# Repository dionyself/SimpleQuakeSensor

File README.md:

# Simple Quake Sensor 
SimpleQuake Sensor is an Earthquake Analyzer. (Work in Progress)  
Useful to capture and analyze Natural EM wave emitions and Earthquake EM emitions.  
The circuit works as an EM ear and broadband receiver  

### Primary EM waves 0 - 40 Hz  
- Ultra Low Frequency: f < 3 Hz  
- Extremely Low Frequency: 3 Hz < f < 3 kHz  
- Very Low Frequency: 3 kHz < f < 30 kHz  

### Secundary Emitions  30 kHz - 5.8 gHz  
- High Frequency: 3 MHz < f < 30 MHz  
- Very High Frequency: 30 MHz < f < 300 MHz    

### Real PCB View (from Kicad 3D viewer)

## How to use it?

1 - Assembly the device  (gerber files provided <here>)  
2 - Connect your device to your audio card / pc using this <> cable  
3 - Connect your device's input to ground using 2 probes and a good coaxial cable <example>  
4 - Take audio samples as you like: `parec raw_sample.raw --file-format=raw` ( Linux command )  
              or    
5 - Use your favorite Audio analizer to listen and view the live data `jaaa -A -d hw:1`  

### My Results

I have included images, screenshoots and audio files captured during relevant events:  

a) 0 - 1.5 kHz

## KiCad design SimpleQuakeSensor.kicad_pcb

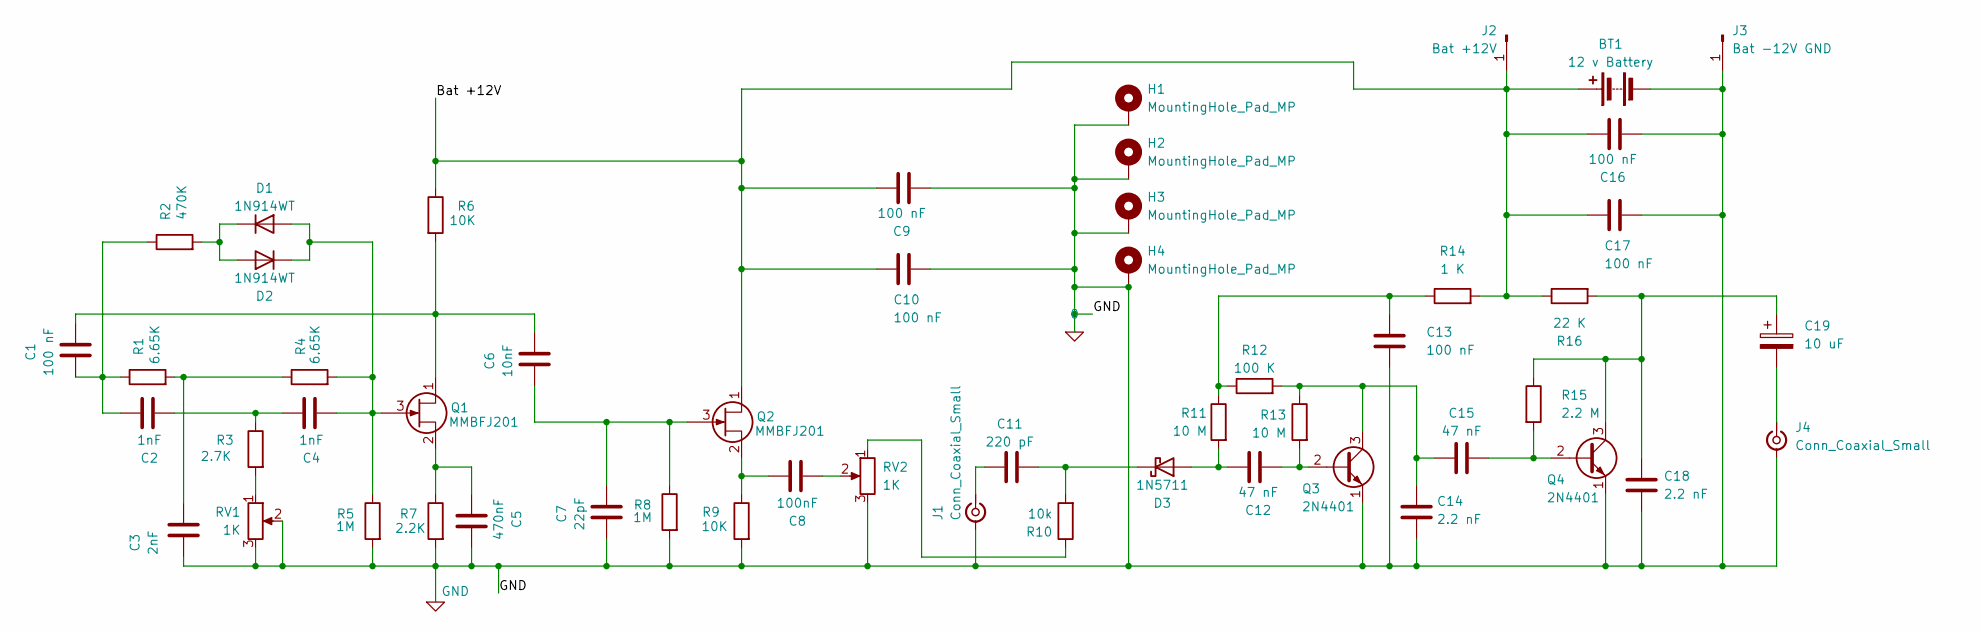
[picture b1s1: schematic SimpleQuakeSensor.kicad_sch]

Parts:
BT1: 12 v Battery
C1, C9, C10, C13, C16, C17: 100 nF; C_0805_2012Metric
C2, C4: 1nF; C_0805_2012Metric
C3: 2nF; C_0805_2012Metric
C5: 470nF; C_0805_2012Metric
C6: 10nF; C_0805_2012Metric
C7: 22pF; C_0805_2012Metric
C8: 100nF; C_0805_2012Metric
C11: 220 pF; C_0805_2012Metric
C12, C15: 47 nF; C_0805_2012Metric
C14, C18: 2.2 nF; C_0805_2012Metric
C19: 10 uF; CP_EIA-2012-15_AVX-P
D1, D2: 1N914WT; D_0805_2012Metric
D3: 1N5711; D_0805_2012Metric
H1, H2, H3, H4: MountingHole_Pad_MP; MountingHole_2.2mm_M2_DIN965_Pad_TopBottom
J1, J4: Conn_Coaxial_Small; SMA_Molex_73251-1153_EdgeMount_Horizontal
J2: Bat +12V; PinHeader_1x01_P2.54mm_Vertical_2_FMD
J3: Bat -12V GND; PinHeader_1x01_P2.54mm_Vertical_2_FMD
Q1, Q2: MMBFJ201; SOT-23-3
Q3, Q4: 2N4401; SOT-23-3
R1, R4: 6.65K; R_0805_2012Metric
R2: 470K; R_0805_2012Metric
R3: 2.7K; R_0805_2012Metric
R5, R8: 1M; R_0805_2012Metric
R6, R9: 10K; R_0805_2012Metric
R7: 2.2K; R_0805_2012Metric
R10: 10k; R_0805_2012Metric
R11, R13: 10 M; R_0805_2012Metric
R12: 100 K; R_0805_2012Metric
R14: 1 K; R_0805_2012Metric
R15: 2.2 M; R_0805_2012Metric
R16: 22 K; R_0805_2012Metric
RV1, RV2: 1K; Potentiometer_Bourns_TC33X_Vertical

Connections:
0: BT1.2 (-), C3.1, C5.1, C7.2, C9.2, C10.1, C13.2, C14.2, C16.2, C17.1, C18.2, H1.MP (MP_MP), H2.MP (MP_MP), H3.MP (MP_MP), H4.MP (MP_MP), J1.2 (Ext), J3.1 (Pin_1_1), J4.2 (Ext), Q3.1 (E), Q4.1 (E), R5.2, R7.2, R8.2, R9.2, RV1.2, RV1.3, RV2.3
/Bat +12V: BT1.1 (+), C9.1, C10.2, C16.1, C17.2, J2.1 (Pin_1_1), Q2.1 (D), R6.1, R14.2, R16.1
unnamed: C1.2, C2.1, R1.1, R2.1
unnamed: C2.2, C4.1, R3.1
unnamed: C3.2, R1.2, R4.1
unnamed: C8.2, RV2.2
unnamed: C13.1, R11.1, R12.1, R14.1
unnamed: C4.2, D1.2 (A), D2.1 (K), Q1.3 (G), R4.2, R5.1
unnamed: D1.1 (K), D2.2 (A), R2.2
unnamed: C12.1, D3.2 (A), R11.2
unnamed: C11.2, D3.1 (K), R10.2
unnamed: C11.1, J1.1 (In)
unnamed: C19.2, J4.1 (In)
unnamed: C1.1, C6.1, Q1.1 (D), R6.2
unnamed: C5.2, Q1.2 (S), R7.1
unnamed: C6.2, C7.1, Q2.3 (G), R8.1
unnamed: C8.1, Q2.2 (S), R9.1
unnamed: C12.2, Q3.2 (B), R13.2
unnamed: C14.1, C15.2, Q3.3 (C), R12.2, R13.1
unnamed: C15.1, Q4.2 (B), R15.2
unnamed: C18.1, C19.1, Q4.3 (C), R15.1, R16.2
unnamed: R3.2, RV1.1
unnamed: R10.1, RV2.1

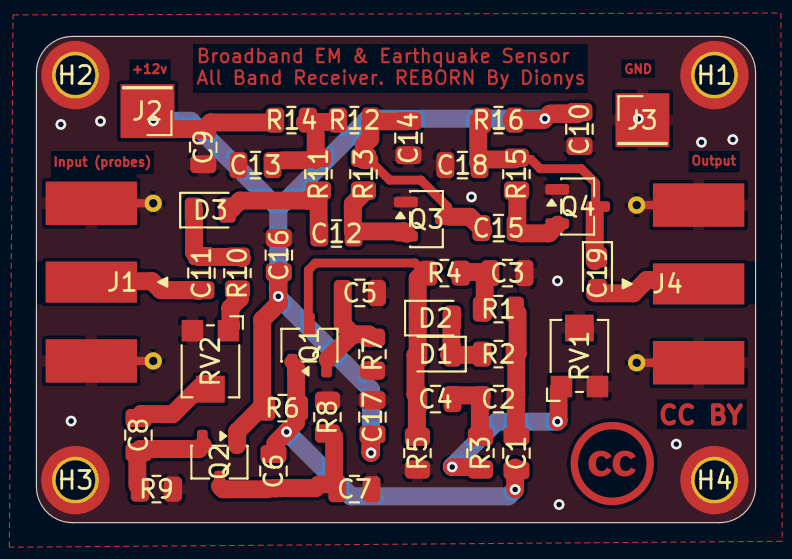
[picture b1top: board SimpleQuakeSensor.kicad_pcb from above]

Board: 2 copper layers, 39.9 x 27.0 mm, 52 parts (0 on the bottom side), 23 nets.

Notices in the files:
SimpleQuakeSensor.kicad_pcb:
CC BY
